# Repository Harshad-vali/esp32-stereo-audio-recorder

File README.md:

# ESP32 Audio Device

Hardware design files for an ESP32-based audio recording device, including the KiCad project, PCB layout, schematic, manufacturing Gerbers, bill of materials, and design renders.

- **Revision:** v1.0
- **Date:** 10-03-2026
- **Designed by:** Harshad Vali
- **Organization:** Suretrust

## 3D Views

![3D Side View](https://github.com/Harshad-vali/esp32-stereo-audio-recorder/blob/b32badf5ee24e91bf9460e6525b27791062b05e6/side%20view.png
)

## Overview

This board is an ESP32-based audio module designed around an **ESP32-WROOM-32** controller. The schematic integrates stereo digital microphone inputs, microSD storage, a real-time clock, and a regulated 3.3 V power system.

The PCB is approximately **62.5 mm × 44 mm** with a **1.6 mm board thickness**. The layout includes four mounting holes and dedicated areas for the antenna, microphone section, power circuitry, ESP32 module, and microSD card socket.

## Key Features

- **ESP32-WROOM-32** as the main controller
- **Two ICS-43434 I2S MEMS microphones** for stereo audio input
- **ST-TF-003A microSD socket** for removable storage
- **DS3232M RTC** for real-time clock functionality
- **TPS54331D** switching regulator for the 3.3 V power rail
- **Barrel-jack power input** with battery support
- **Push-button input** for the ESP32 control circuit
- Dedicated antenna keepout / antenna area
- Dedicated microphone section
- Four PCB mounting holes
- Manufacturing-ready Gerber and drill files

## Design Details

The schematic is divided into the following functional sections:

- **Power Circuit** — input power, filtering, protection, and 3.3 V regulation
- **ESP32 Controller** — ESP32-WROOM-32 and associated control circuitry
- **Microphone Section** — two ICS-43434 digital MEMS microphones
- **MicroSD Socket** — ST-TF-003A storage interface
- **RTC Circuit** — DS3232M real-time clock with battery backup

### Main Components

| Function | Component |
|---|---|
| Microcontroller | ESP32-WROOM-32 |
| Stereo audio input | 2 × ICS-43434 |
| Storage | ST-TF-003A microSD socket |
| Real-time clock | DS3232M |
| Power regulator | TPS54331D |
| Power protection | B340 Schottky diode |
| Power input | Barrel jack |
| Battery | Battery_Cell |
| User input | Push button |
| Inductor | 6.8 µH |

## PCB Layout

The PCB layout contains dedicated placement areas for the main functional blocks. The ESP32 is positioned near the upper portion of the board, with the microphone section located near the RF/antenna area and the microSD socket along the lower portion of the board.

The design screenshot shows **189 pads, 119 vias, 251 track segments, 53 nets, and 0 unrouted connections** in the displayed PCB state.

.png)

## Copper Layers

### Front Copper Layer

### Back Copper Layer

### All Copper Layers

## Assembly Layers

### Front Assembly

### Back Assembly

## Schematic

The complete design schematic contains the power circuit, ESP32 controller, microphone section, microSD interface, and RTC circuit.

## Board Dimensions

- **Board size:** approximately 62.5 mm × 44 mm
- **PCB thickness:** 1.6 mm
- **Mounting holes:** 4
- **Board outline:** Rounded corners

## Manufacturing

The `esp32 audio device gerber` folder contains the manufacturing outputs required for PCB fabrication:

- Front copper (`F_Cu`)
- Back copper (`B_Cu`)
- Front solder mask (`F_Mask`)
- Back solder mask (`B_Mask`)
- Front paste (`F_Paste`)
- Back paste (`B_Paste`)
- Front silkscreen (`F_Silkscreen`)
- Back silkscreen (`B_Silkscreen`)
- Edge cuts (`Edge_Cuts`)
- Plated-through-hole drill file (`PTH.drl`)
- Non-plated-through-hole drill file (`NPTH.drl`)
- Gerber job file (`job.gbrjob`)

## Files in This Repo

- `esp32 audio device main file/` — KiCad project files
  - `aduio device [roject.kicad_pro` — KiCad project
  - `aduio device [roject.kicad_sch` — schematic
  - `aduio device [roject.kicad_pcb` — PCB layout
  - `aduio device [roject.kicad_prl` — local KiCad project settings
  - `aduio device [roject-backups/` — KiCad backup archive
- `esp32 audio device gerber/` — PCB manufacturing Gerbers and drill files
- `esp32 audio device main bom.xlsx` — bill of materials
- `*.png` — PCB renders, layer views, assembly views, and schematic preview

## Tools Used

- **KiCad** — schematic capture and PCB layout
- **Excel / spreadsheet BOM** — component and manufacturing part information

## Opening the Project

Open the `.kicad_pro` file with **KiCad** to view and edit the complete project.

The project contains the schematic and PCB layout in KiCad-native formats, along with the generated manufacturing files.

## Notes

- The project files retain the original filenames from the supplied project archive.
- The Gerber files are generated from the supplied PCB layout.
- The BOM contains component references, values, footprints, quantities, manufacturer information, and part numbers.
- Backup archives are included in the supplied project and are not required for normal PCB editing.

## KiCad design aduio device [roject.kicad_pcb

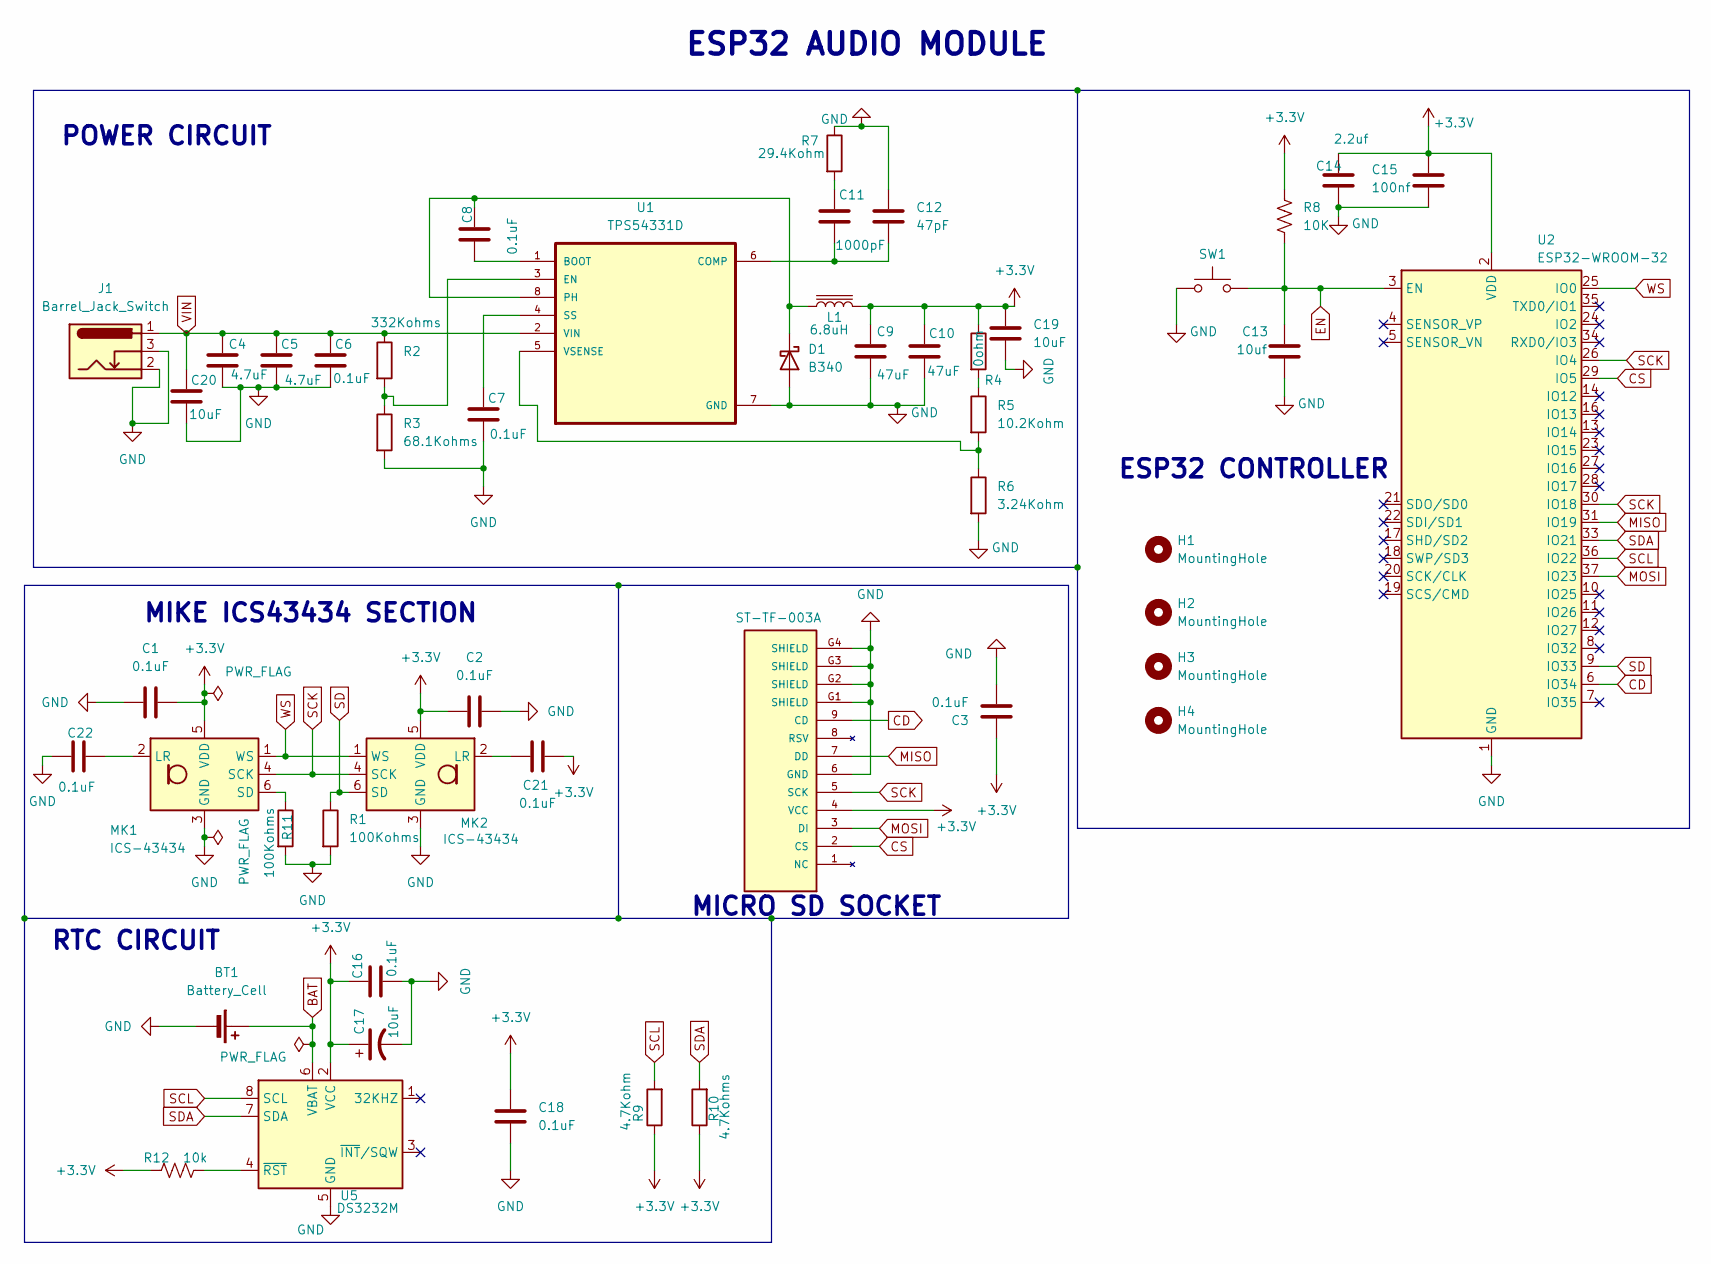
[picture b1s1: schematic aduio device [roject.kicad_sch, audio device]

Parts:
BT1: Battery_Cell; BatteryHolder_Keystone_3000_1x12mm
C1, C2, C3, C6, C7, C8, C16, C18, C21, C22: 0.1uF; C_0805_2012Metric
C4, C5: 4.7uF; C_0805_2012Metric
C9, C10: 47uF; C_0805_2012Metric
C11: 1000pF; C_0805_2012Metric
C12: 47pF; C_0805_2012Metric
C13: 10uf; CP_EIA-6032-15_Kemet-U
C14: 2.2uf; C_0805_2012Metric
C15: 100nf; C_0805_2012Metric
C17, C19, C20: 10uF; CP_EIA-6032-15_Kemet-U
D1: B340; D_SMC
H1, H2, H3, H4: MountingHole; MountingHole_2.1mm
J1: Barrel_Jack_Switch; BarrelJack_Horizontal
L1: 6.8uH; L_0805_2012Metric
MK1, MK2: ICS-43434; InvenSense_ICS-43434-6_3.5x2.65mm
P1: ST-TF-003A; micro sd socket
R1, R11: 100Kohms; R_0805_2012Metric
R2: 332Kohms; R_0805_2012Metric
R3: 68.1Kohms; R_0805_2012Metric
R4: 0ohm; R_0805_2012Metric
R5: 10.2Kohm; R_0805_2012Metric
R6: 3.24Kohm; R_0805_2012Metric
R7: 29.4Kohm; R_0805_2012Metric
R8: 10K; R_0805_2012Metric
R9: 4.7Kohm; R_0805_2012Metric
R10: 4.7Kohms; R_0805_2012Metric
R12: 10k; R_0805_2012Metric
SW1: SW_Push; SW_Push_SPST_NO_Alps_SKRK
U1: TPS54331D
U2: ESP32-WROOM-32
U5: DS3232M; SOIC-8_3.9x4.9mm_P1.27mm

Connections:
+3.3V: C1.2, C2.1, C3.1, C9.1, C10.1, C14.1, C15.1, C16.1, C17.1, C18.1, C19.1, C21.2, L1.2, MK1.5 (VDD), MK2.5 (VDD), P1.4 (VCC), R4.1, R8.1, R9.1, R10.1, R12.1, U2.2 (VDD), U5.2 (VCC)
BAT: BT1.1 (+), U5.6 (VBAT)
CD: P1.9 (CD), U2.6 (IO34)
CS: P1.2 (CS), U2.29 (IO5)
EN: C13.1, R8.2, SW1.2, U2.3 (EN)
GND: BT1.2 (-), C1.1, C2.2, C3.2, C4.2, C5.2, C6.2, C7.2, C9.2, C10.2, C12.1, C13.2, C14.2, C15.2, C16.2, C17.2, C18.2, C19.2, C20.2, C22.1, D1.2 (A), J1.2, J1.3, MK1.3 (GND), MK2.3 (GND), P1.6 (GND), P1.G1 (SHIELD), P1.G2 (SHIELD), P1.G3 (SHIELD), P1.G4 (SHIELD), R1.2, R3.2, R6.2, R7.1, R11.2, SW1.1, U1.7 (GND), U2.1 (GND), U2.15 (GND), U2.38 (GND), U2.39 (GND), U5.5 (GND)
MISO: P1.7 (DD), U2.31 (IO19)
MOSI: P1.3 (DI), U2.37 (IO23)
unnamed: C11.1, R7.2
unnamed: C8.2, D1.1 (K), L1.1, U1.8 (PH)
unnamed: C22.2, MK1.2 (LR)
unnamed: MK1.6 (SD), R11.1
unnamed: C21.1, MK2.2 (LR)
unnamed: R4.2, R5.1
unnamed: C8.1, U1.1 (BOOT)
unnamed: C11.2, C12.2, U1.6 (COMP)
unnamed: R2.2, R3.1, U1.3 (EN)
unnamed: C7.1, U1.4 (SS)
unnamed: R5.2, R6.1, U1.5 (VSENSE)
unnamed: R12.2, U5.4 (~RST)
SCK: MK1.4 (SCK), MK2.4 (SCK), P1.5 (SCK), U2.26 (IO4), U2.30 (IO18)
SCL: R9.2, U2.36 (IO22), U5.8 (SCL)
SD: MK2.6 (SD), R1.1, U2.9 (IO33)
SDA: R10.2, U2.33 (IO21), U5.7 (SDA)
VIN: C4.1, C5.1, C6.1, C20.1, J1.1, R2.1, U1.2 (VIN)
WS: MK1.1 (WS), MK2.1 (WS), U2.25 (IO0)

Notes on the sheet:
ESP32 AUDIO MODULE
RTC CIRCUIT
POWER CIRCUIT
ESP32 CONTROLLER
MICRO SD SOCKET
MIKE ICS43434 SECTION

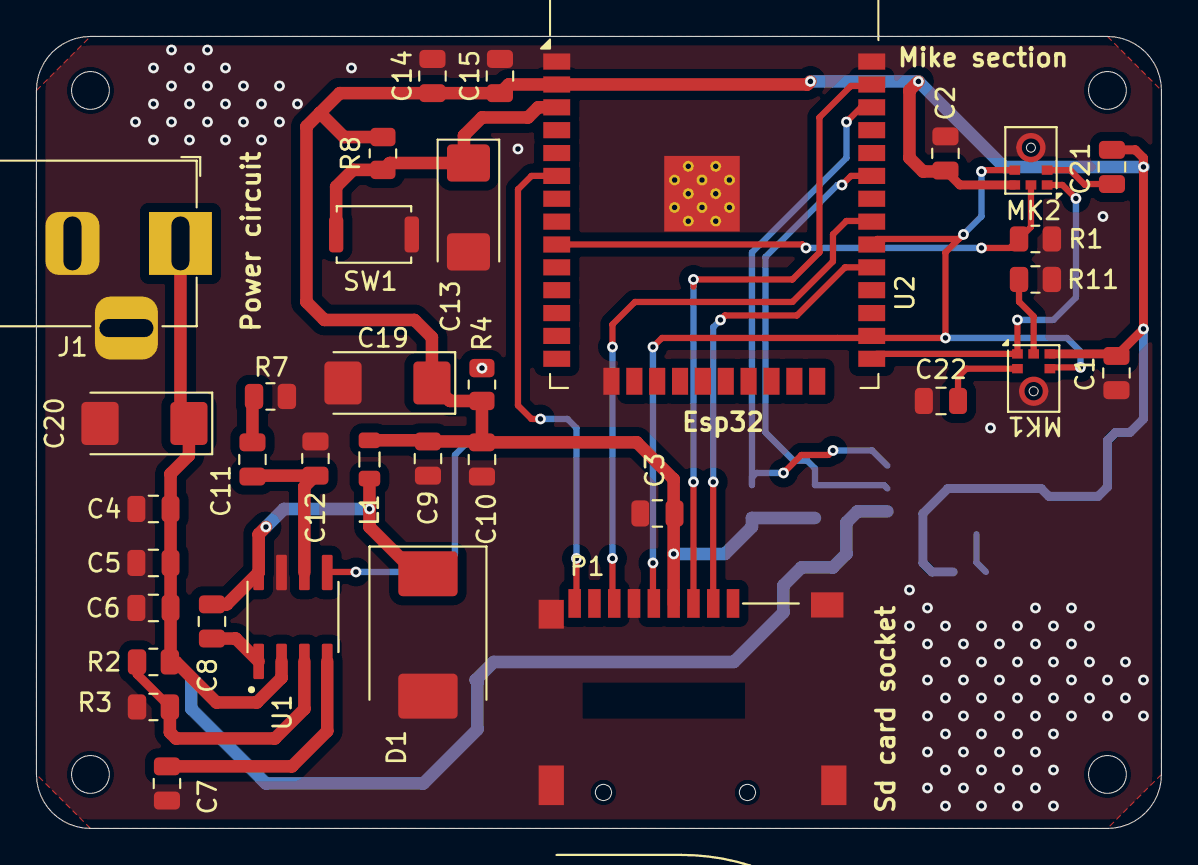
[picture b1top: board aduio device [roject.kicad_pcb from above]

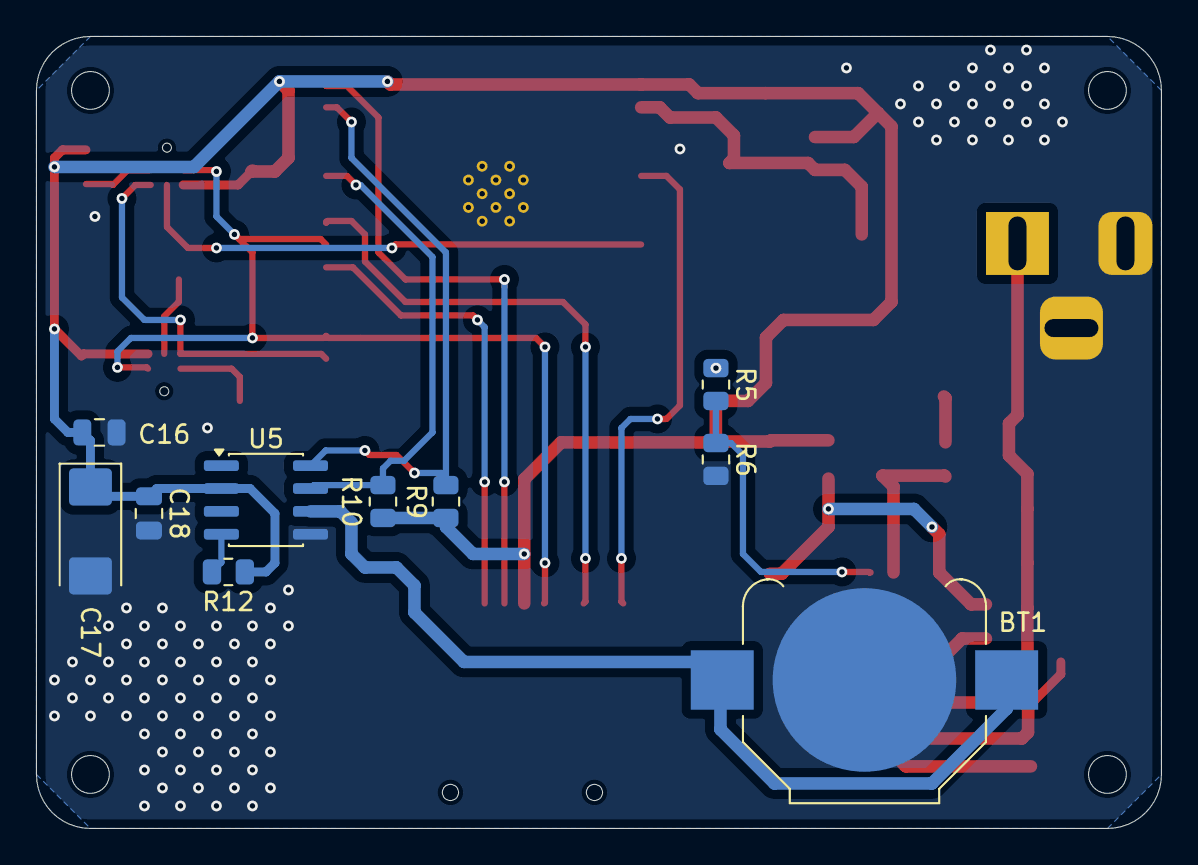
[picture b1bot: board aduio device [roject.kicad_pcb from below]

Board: 2 copper layers, 62.5 x 44.0 mm, 49 parts (10 on the bottom side), 26 nets.
